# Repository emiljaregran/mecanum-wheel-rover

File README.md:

# mecanum-wheel-rover
A mecanum wheel rover built during a 2 week project.

The wheels are a remix of https://www.thingiverse.com/thing:2473

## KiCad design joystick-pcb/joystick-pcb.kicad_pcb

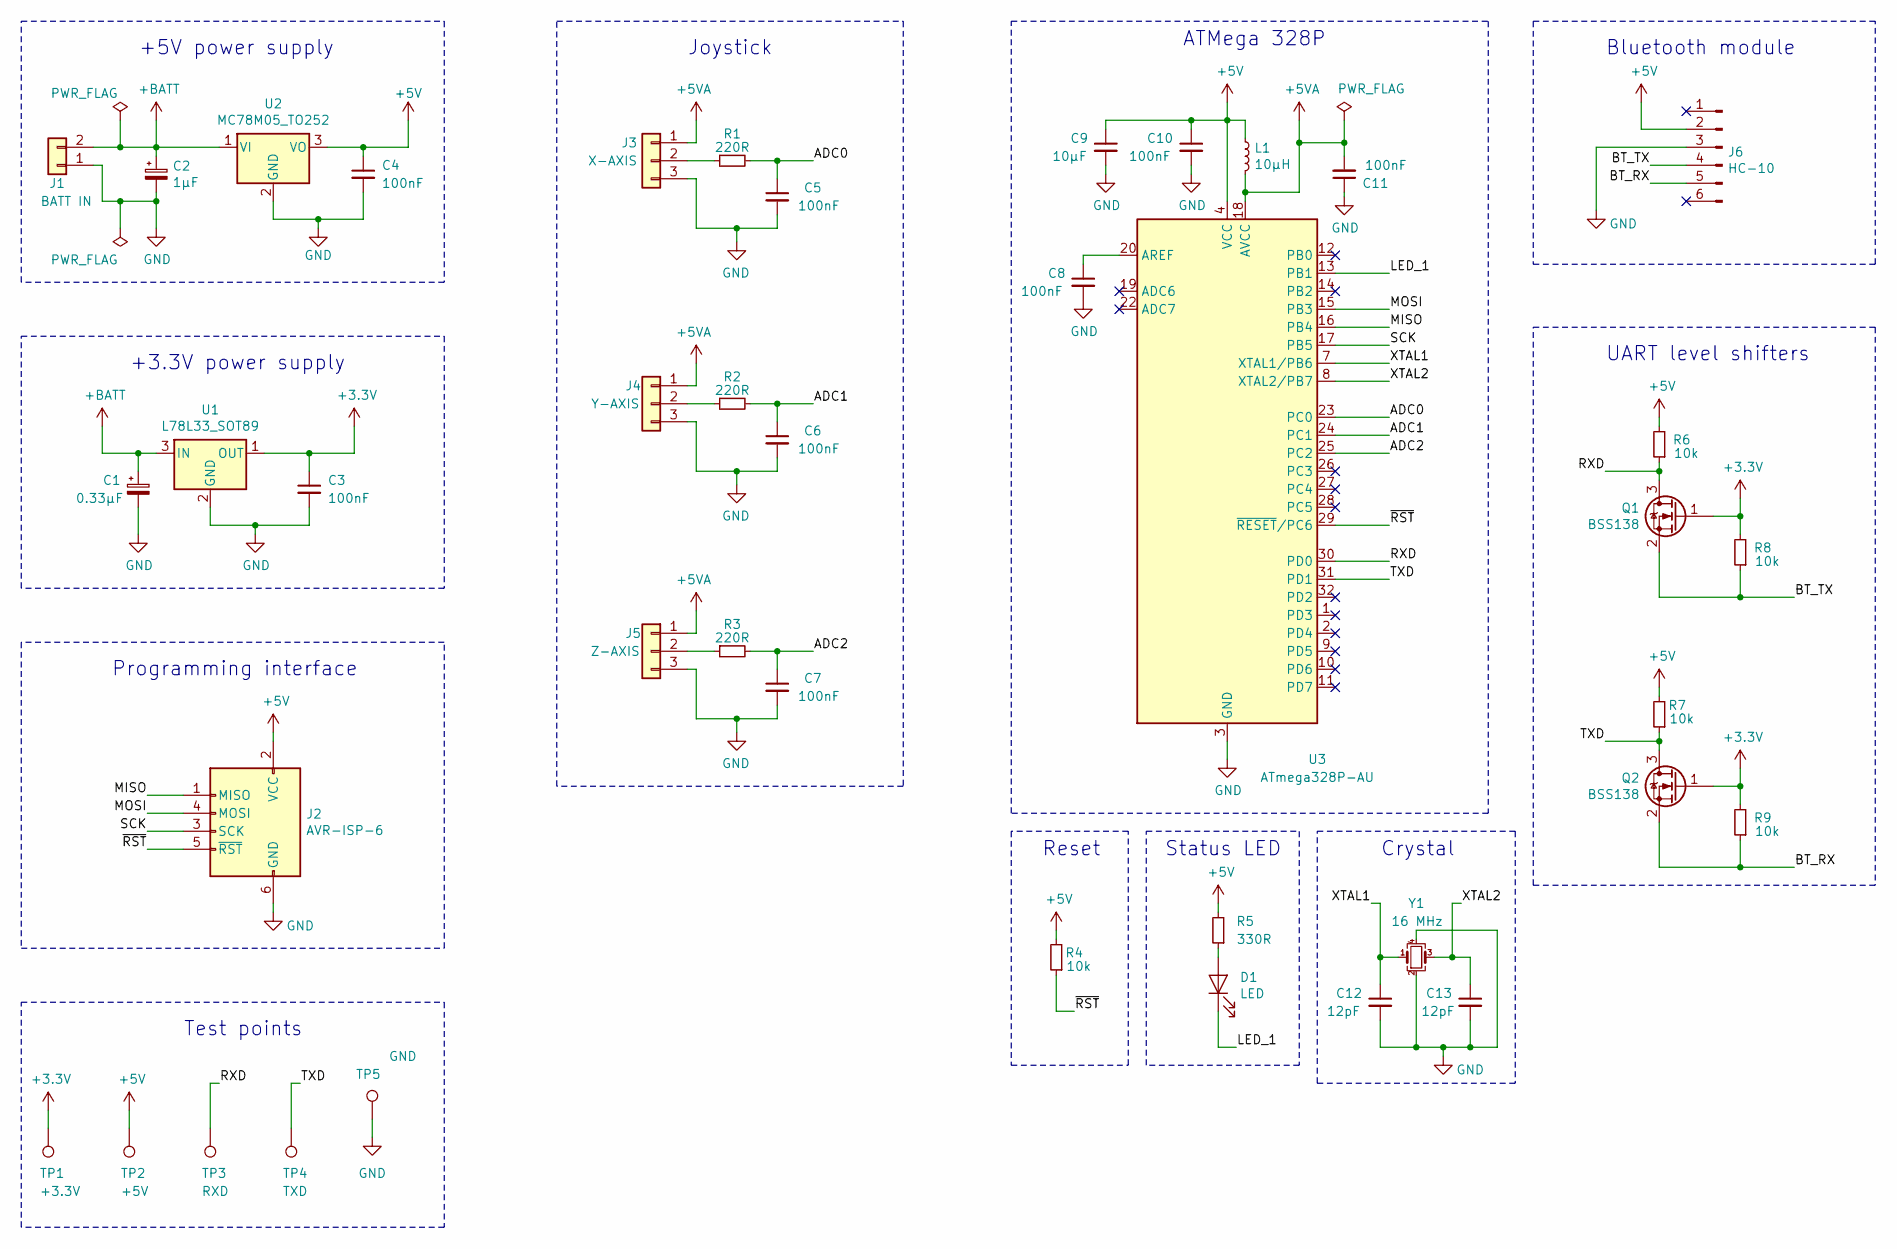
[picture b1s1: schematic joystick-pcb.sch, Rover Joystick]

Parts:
C1: 0.33μF; C_1206_3216Metric_Pad1.42x1.75mm_HandSolder
C2: 1μF; C_1206_3216Metric_Pad1.42x1.75mm_HandSolder
C3, C4, C5, C6, C7, C8, C10, C11: 100nF; C_0603_1608Metric_Pad1.05x0.95mm_HandSolder
C9: 10μF; C_1210_3225Metric_Pad1.42x2.65mm_HandSolder
C12, C13: 12pF; C_0603_1608Metric_Pad1.05x0.95mm_HandSolder
D1: LED; LED_0805_2012Metric_Pad1.15x1.40mm_HandSolder
J1: BATT IN; TerminalBlock_Phoenix_MKDS-1,5-2-5.08_1x02_P5.08mm_Horizont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
J2: AVR-ISP-6; IDC-Header_2x03_P2.54mm_Vertical
J3: X-AXIS; PinHeader_1x03_P2.54mm_Vertical
J4: Y-AXIS; PinHeader_1x03_P2.54mm_Vertical
J5: Z-AXIS; PinHeader_1x03_P2.54mm_Vertical
J6: HC-10; PinHeader_1x06_P2.54mm_Vertical
L1: 10μH; L_0805_2012Metric_Pad1.15x1.40mm_HandSolder
Q1, Q2: BSS138; SOT-23
R1, R2, R3: 220R; R_0603_1608Metric_Pad1.05x0.95mm_HandSolder
R4, R6, R7, R8, R9: 10k; R_0603_1608Metric_Pad1.05x0.95mm_HandSolder
R5: 330R; R_0603_1608Metric_Pad1.05x0.95mm_HandSolder
TP1: +3.3V; TestPoint_THTPad_D2.0mm_Drill1.0mm
TP2: +5V; TestPoint_THTPad_D2.0mm_Drill1.0mm
TP3: RXD; TestPoint_THTPad_D2.0mm_Drill1.0mm
TP4: TXD; TestPoint_THTPad_D2.0mm_Drill1.0mm
TP5: GND; TestPoint_THTPad_D2.0mm_Drill1.0mm
U1: L78L33_SOT89; SOT-89-3
U2: MC78M05_TO252; TO-252-2
U3: ATmega328P-AU; TQFP-32_7x7mm_P0.8mm
Y1: 16 MHz; Crystal_SMD_EuroQuartz_MJ-4Pin_5.0x3.2mm_HandSoldering

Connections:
+3V3: C3.1, Q1.1 (G), Q2.1 (G), R8.2, R9.2, TP1.1, U1.1 (OUT)
+5V: C4.1, C9.1, C10.1, J2.2 (VCC), J6.2, L1.1, R4.2, R5.2, R6.2, R7.2, TP2.1, U2.3 (VO), U3.4 (VCC), U3.6 (VCC)
+5VA: C11.2, J3.1, J4.1, J5.1, L1.2, U3.18 (AVCC)
+BATT: C1.1, C2.1, J1.2, U1.3 (IN), U2.1 (VI)
/ADC0: C5.1, R1.2, U3.23 (PC0)
/ADC1: C6.1, R2.2, U3.24 (PC1)
/ADC2: C7.1, R3.2, U3.25 (PC2)
/BT_RX: J6.5, Q2.2 (S), R9.1
/BT_TX: J6.4, Q1.2 (S), R8.1
/LED_1: D1.1 (K), U3.13 (PB1)
/MISO: J2.1 (MISO), U3.16 (PB4)
/MOSI: J2.4 (MOSI), U3.15 (PB3)
/RXD: Q1.3 (D), R6.1, TP3.1, U3.30 (PD0)
/SCK: J2.3 (SCK), U3.17 (PB5)
/TXD: Q2.3 (D), R7.1, TP4.1, U3.31 (PD1)
/XTAL1: C12.1, U3.7 (XTAL1/PB6), Y1.1
/XTAL2: C13.1, U3.8 (XTAL2/PB7), Y1.3
/~RST: J2.5 (~RST), R4.1, U3.29 (~RESET~/PC6)
GND: C1.2, C2.2, C3.2, C4.2, C5.2, C6.2, C7.2, C8.2, C9.2, C10.2, C11.1, C12.2, C13.2, J1.1, J2.6 (GND), J3.3, J4.3, J5.3, J6.3, TP5.1, U1.2 (GND), U2.2 (GND), U3.3 (GND), U3.5 (GND), U3.21 (GND), Y1.2, Y1.4
unnamed: C8.1, U3.20 (AREF)
unnamed: D1.2 (A), R5.1
unnamed: J3.2, R1.1
unnamed: J4.2, R2.1
unnamed: J5.2, R3.1

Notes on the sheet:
UART level shifters
Bluetooth module
+5V power supply
+3.3V power supply
Programming interface
Test points
Crystal
ATMega 328P
Status LED
Reset
Joystick

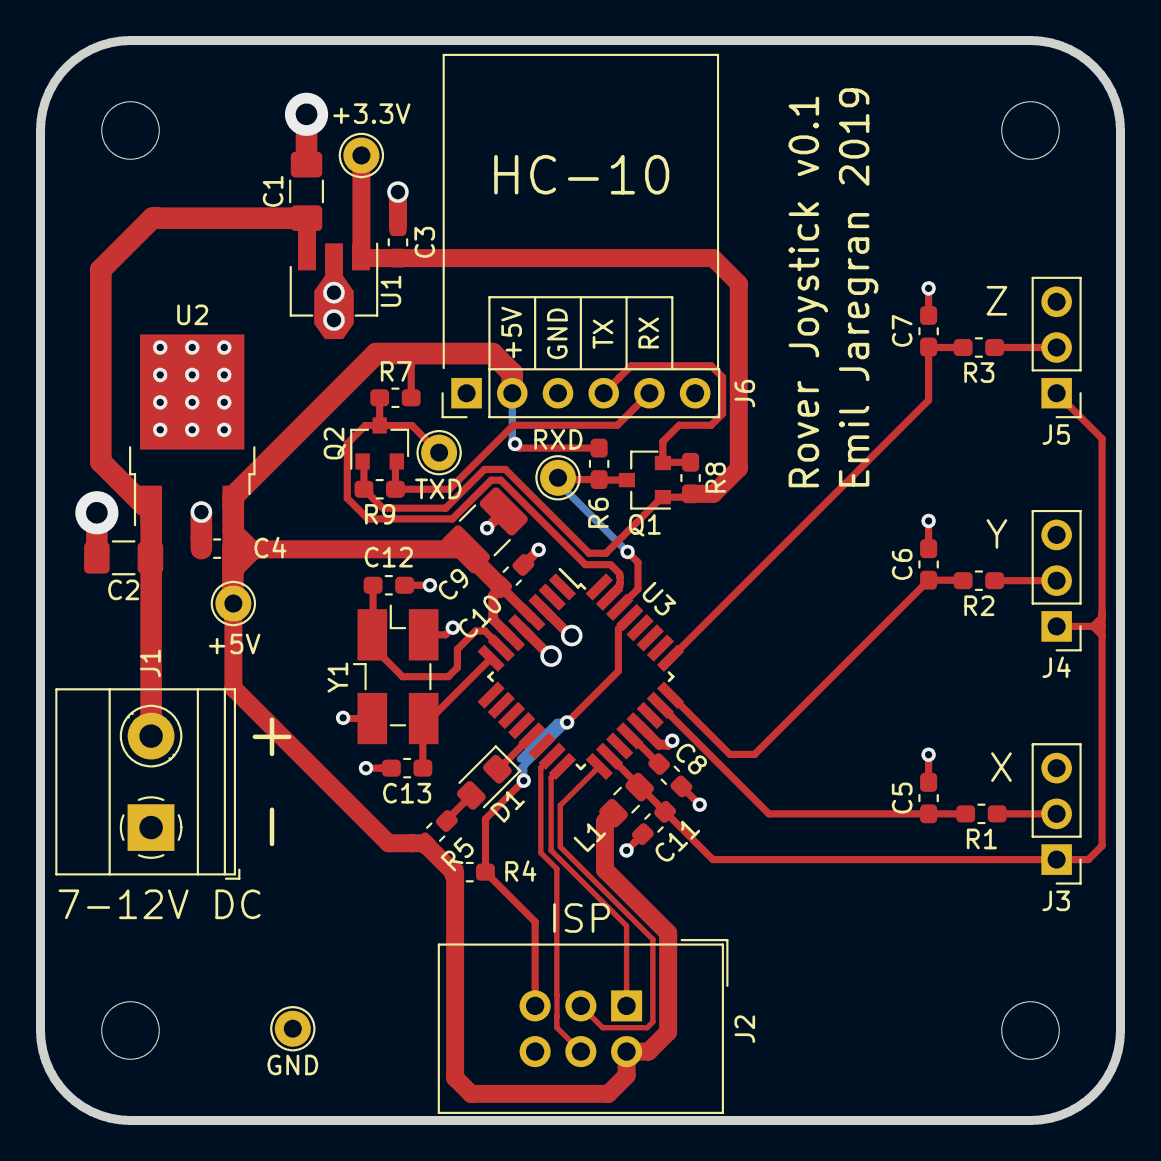
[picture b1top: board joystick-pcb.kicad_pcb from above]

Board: 2 copper layers, 60.0 x 60.0 mm, 41 parts (0 on the bottom side), 24 nets.

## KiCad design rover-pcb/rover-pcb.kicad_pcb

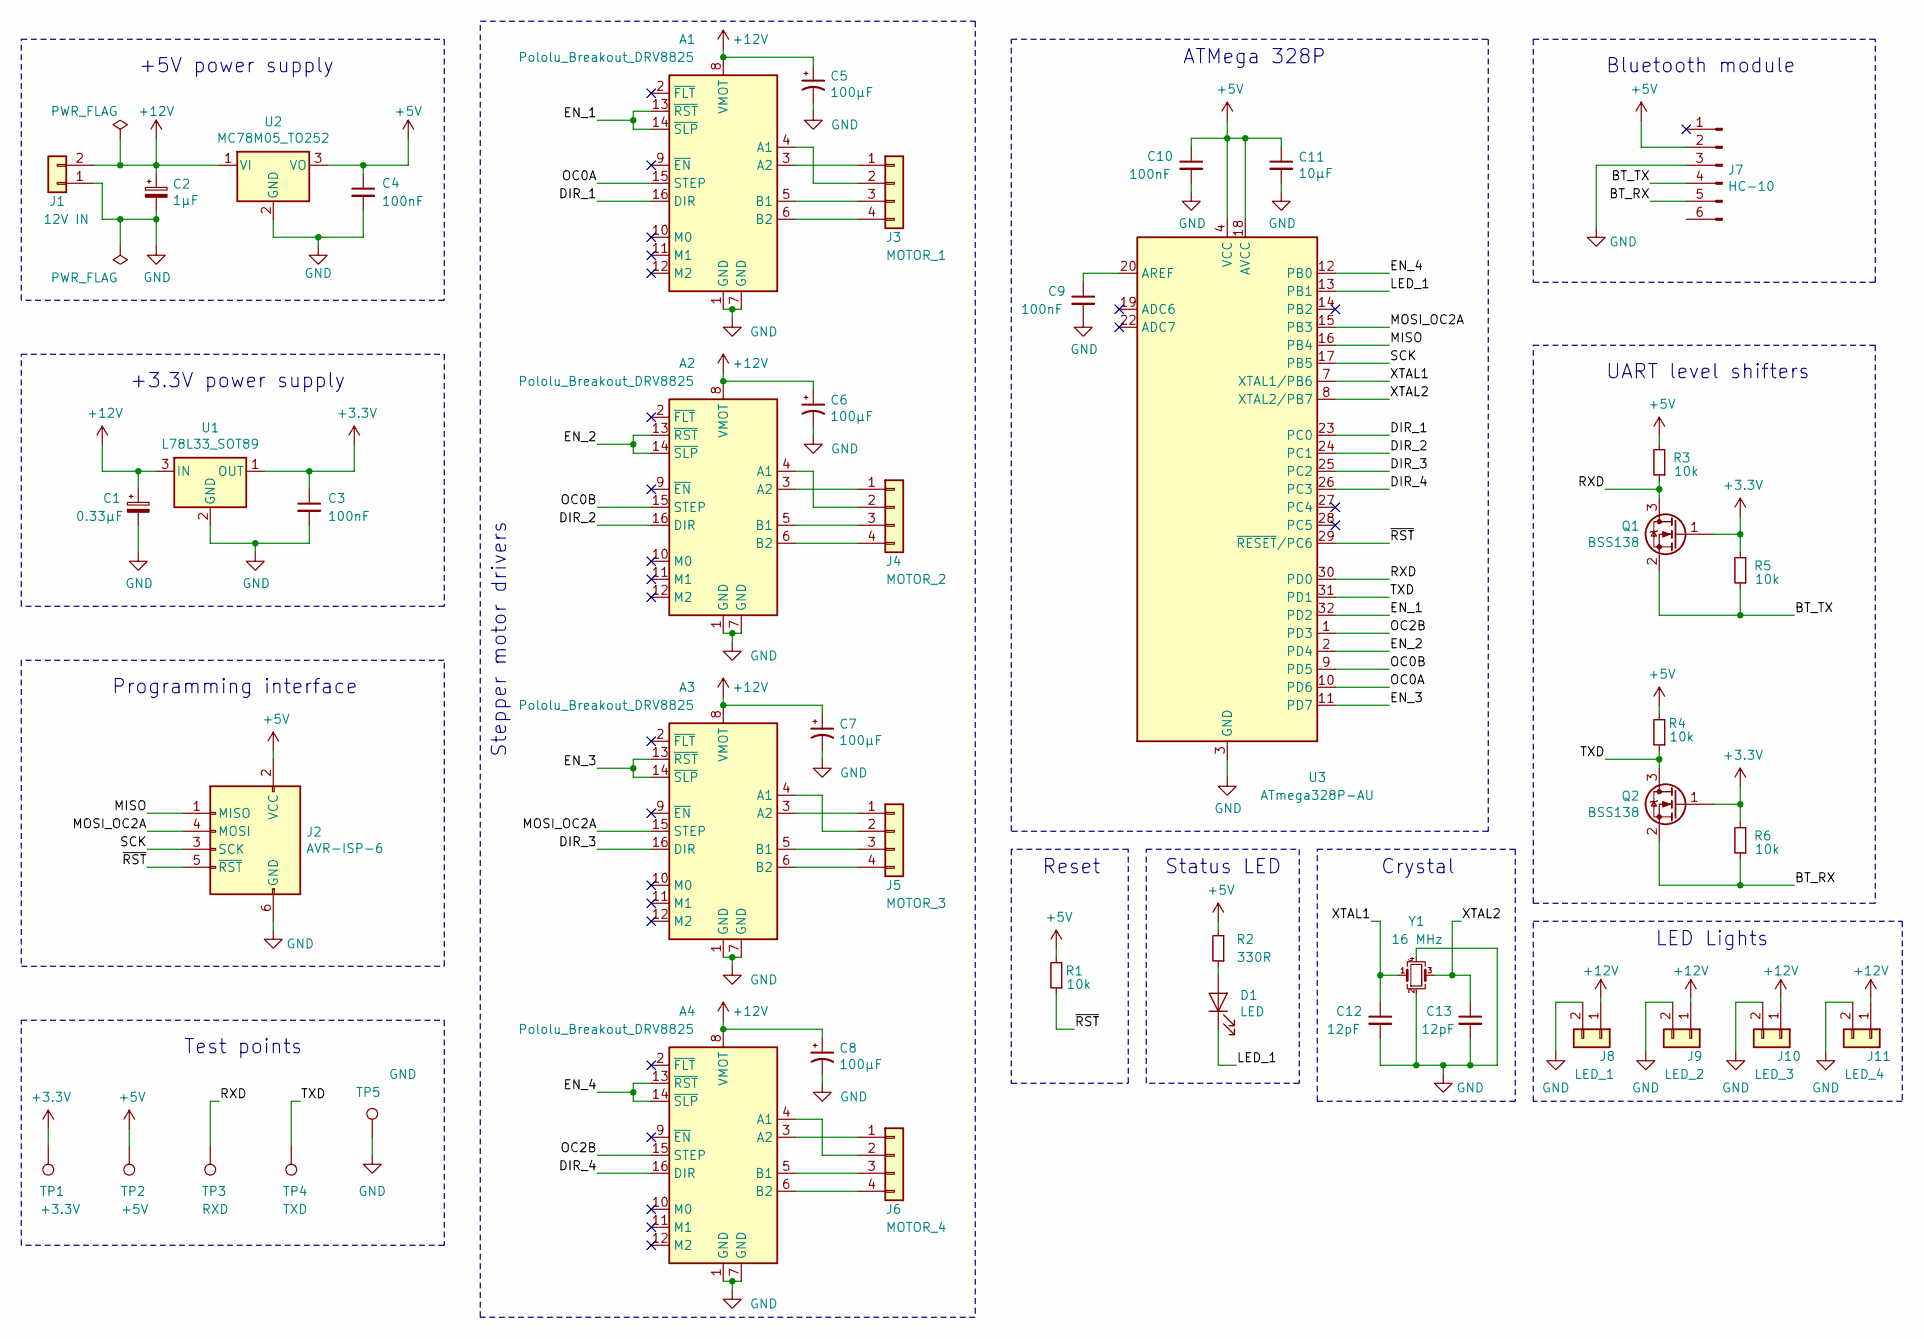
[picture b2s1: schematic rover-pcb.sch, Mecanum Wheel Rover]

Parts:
A1, A2, A3, A4: Pololu_Breakout_DRV8825; Pololu_Breakout-16_15.2x20.3mm
C1: 0.33μF; C_1206_3216Metric_Pad1.42x1.75mm_HandSolder
C2: 1μF; C_1206_3216Metric_Pad1.42x1.75mm_HandSolder
C3, C4, C9, C10: 100nF; C_0603_1608Metric_Pad1.05x0.95mm_HandSolder
C5, C6, C7, C8: 100μF; CP_Elec_6.3x7.7
C11: 10μF; C_1210_3225Metric_Pad1.42x2.65mm_HandSolder
C12, C13: 12pF; C_0603_1608Metric_Pad1.05x0.95mm_HandSolder
D1: LED; LED_0805_2012Metric_Pad1.15x1.40mm_HandSolder
J1: 12V IN; TerminalBlock_Phoenix_MKDS-1,5-2-5.08_1x02_P5.08mm_Horizont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
J2: AVR-ISP-6; IDC-Header_2x03_P2.54mm_Vertical
J3: MOTOR_1; PinHeader_1x04_P2.54mm_Vertical
J4: MOTOR_2; PinHeader_1x04_P2.54mm_Vertical
J5: MOTOR_3; PinHeader_1x04_P2.54mm_Vertical
J6: MOTOR_4; PinHeader_1x04_P2.54mm_Vertical
J7: HC-10; PinHeader_1x06_P2.54mm_Vertical
J8: LED_1; SolderWirePad_1x02_SMD_2x4mm
J9: LED_2; SolderWirePad_1x02_SMD_2x4mm
J10: LED_3; SolderWirePad_1x02_SMD_2x4mm
J11: LED_4; SolderWirePad_1x02_SMD_2x4mm
Q1, Q2: BSS138; SOT-23
R1, R3, R4, R5, R6: 10k; R_0603_1608Metric_Pad1.05x0.95mm_HandSolder
R2: 330R; R_0603_1608Metric_Pad1.05x0.95mm_HandSolder
TP1: +3.3V; TestPoint_THTPad_D2.0mm_Drill1.0mm
TP2: +5V; TestPoint_THTPad_D2.0mm_Drill1.0mm
TP3: RXD; TestPoint_THTPad_D2.0mm_Drill1.0mm
TP4: TXD; TestPoint_THTPad_D2.0mm_Drill1.0mm
TP5: GND; TestPoint_THTPad_D2.0mm_Drill1.0mm
U1: L78L33_SOT89; SOT-89-3
U2: MC78M05_TO252; TO-252-2
U3: ATmega328P-AU; TQFP-32_7x7mm_P0.8mm
Y1: 16 MHz; Crystal_SMD_EuroQuartz_MJ-4Pin_5.0x3.2mm_HandSoldering

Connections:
+3V3: C3.1, Q1.1 (G), Q2.1 (G), R5.2, R6.2, TP1.1, U1.1 (OUT)
+5V: C4.1, C10.1, C11.1, J2.2 (VCC), J7.2, R1.2, R2.2, R3.2, R4.2, TP2.1, U2.3 (VO), U3.4 (VCC), U3.6 (VCC), U3.18 (AVCC)
+12V: A1.8 (VMOT), A2.8 (VMOT), A3.8 (VMOT), A4.8 (VMOT), C1.1, C2.1, C5.1, C6.1, C7.1, C8.1, J1.2, J8.1, J9.1, J10.1, J11.1, U1.3 (IN), U2.1 (VI)
/BT_RX: J7.5, Q2.2 (S), R6.1
/BT_TX: J7.4, Q1.2 (S), R5.1
/DIR_1: A1.16 (DIR), U3.23 (PC0)
/DIR_2: A2.16 (DIR), U3.24 (PC1)
/DIR_3: A3.16 (DIR), U3.25 (PC2)
/DIR_4: A4.16 (DIR), U3.26 (PC3)
/EN_1: A1.13 (~RST), A1.14 (~SLP), U3.32 (PD2)
/EN_2: A2.13 (~RST), A2.14 (~SLP), U3.2 (PD4)
/EN_3: A3.13 (~RST), A3.14 (~SLP), U3.11 (PD7)
/EN_4: A4.13 (~RST), A4.14 (~SLP), U3.12 (PB0)
/LED_1: D1.1 (K), U3.13 (PB1)
/MISO: J2.1 (MISO), U3.16 (PB4)
/MOSI_OC2A: A3.15 (STEP), J2.4 (MOSI), U3.15 (PB3)
/OC0A: A1.15 (STEP), U3.10 (PD6)
/OC0B: A2.15 (STEP), U3.9 (PD5)
/OC2B: A4.15 (STEP), U3.1 (PD3)
/RXD: Q1.3 (D), R3.1, TP3.1, U3.30 (PD0)
/SCK: J2.3 (SCK), U3.17 (PB5)
/TXD: Q2.3 (D), R4.1, TP4.1, U3.31 (PD1)
/XTAL1: C12.1, U3.7 (XTAL1/PB6), Y1.1
/XTAL2: C13.1, U3.8 (XTAL2/PB7), Y1.3
/~RST: J2.5 (~RST), R1.1, U3.29 (~RESET~/PC6)
GND: A1.1 (GND), A1.7 (GND), A2.1 (GND), A2.7 (GND), A3.1 (GND), A3.7 (GND), A4.1 (GND), A4.7 (GND), C1.2, C2.2, C3.2, C4.2, C5.2, C6.2, C7.2, C8.2, C9.2, C10.2, C11.2, C12.2, C13.2, J1.1, J2.6 (GND), J7.3, J8.2, J9.2, J10.2, J11.2, TP5.1, U1.2 (GND), U2.2 (GND), U3.3 (GND), U3.5 (GND), U3.21 (GND), Y1.2, Y1.4
unnamed: A1.3 (A2), J3.1
unnamed: A1.4 (A1), J3.2
unnamed: A1.5 (B1), J3.3
unnamed: A1.6 (B2), J3.4
unnamed: A2.3 (A2), J4.1
unnamed: A2.4 (A1), J4.2
unnamed: A2.5 (B1), J4.3
unnamed: A2.6 (B2), J4.4
unnamed: A3.3 (A2), J5.1
unnamed: A3.4 (A1), J5.2
unnamed: A3.5 (B1), J5.3
unnamed: A3.6 (B2), J5.4
unnamed: A4.3 (A2), J6.1
unnamed: A4.4 (A1), J6.2
unnamed: A4.5 (B1), J6.3
unnamed: A4.6 (B2), J6.4
unnamed: C9.1, U3.20 (AREF)
unnamed: D1.2 (A), R2.1

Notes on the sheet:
UART level shifters
Bluetooth module
+5V power supply
+3.3V power supply
Programming interface
Test points
Crystal
ATMega 328P
Status LED
Stepper motor drivers
Reset
LED Lights

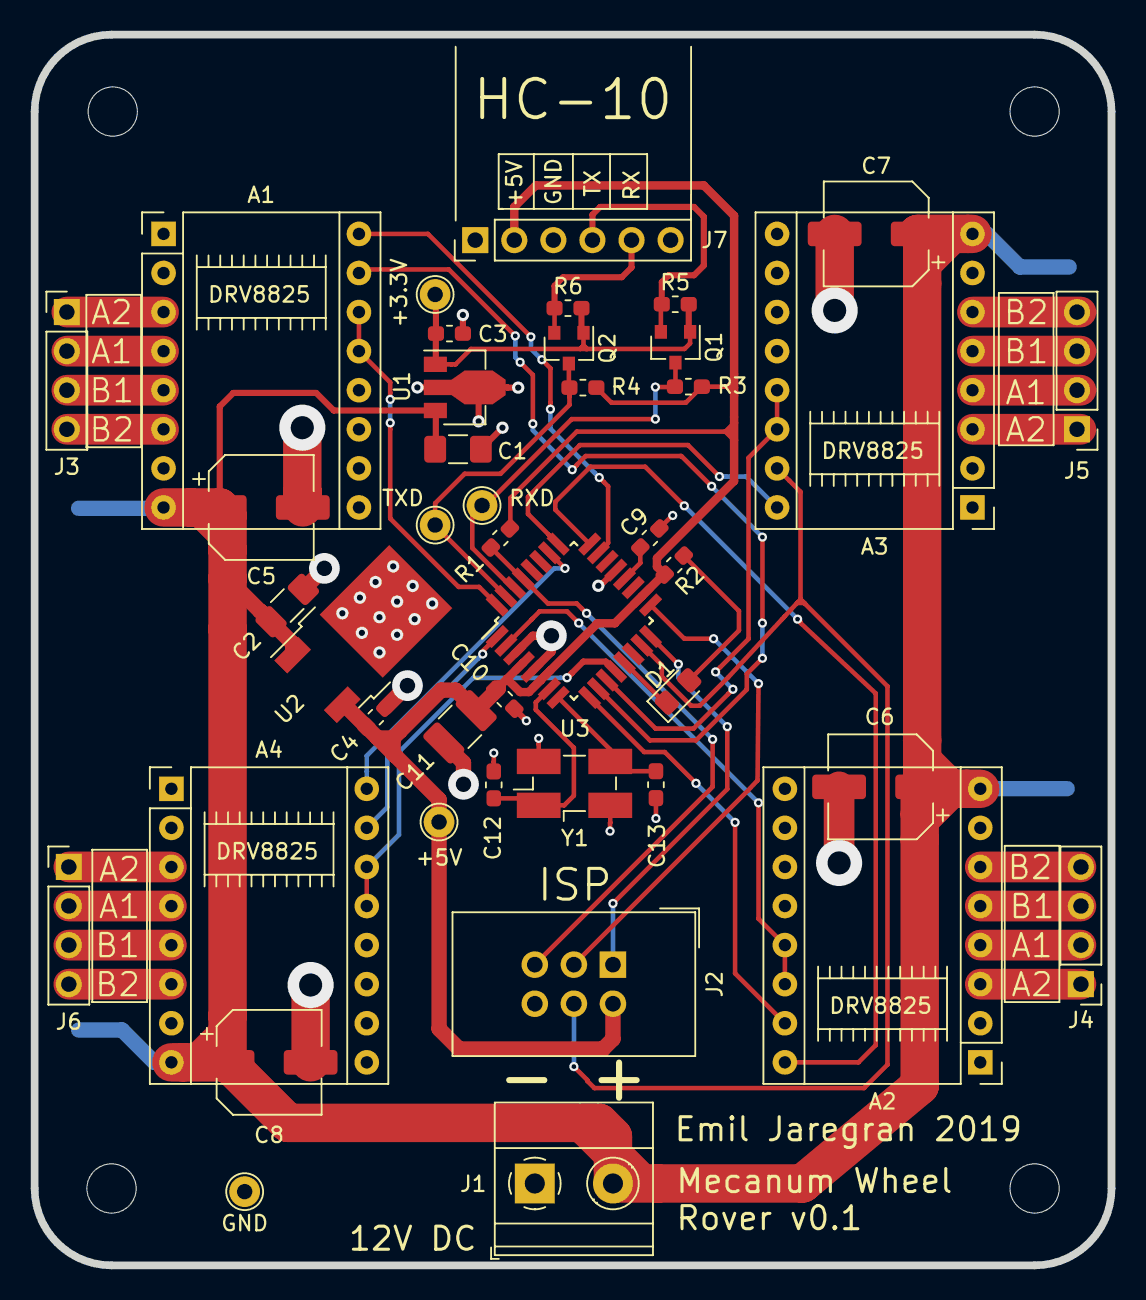
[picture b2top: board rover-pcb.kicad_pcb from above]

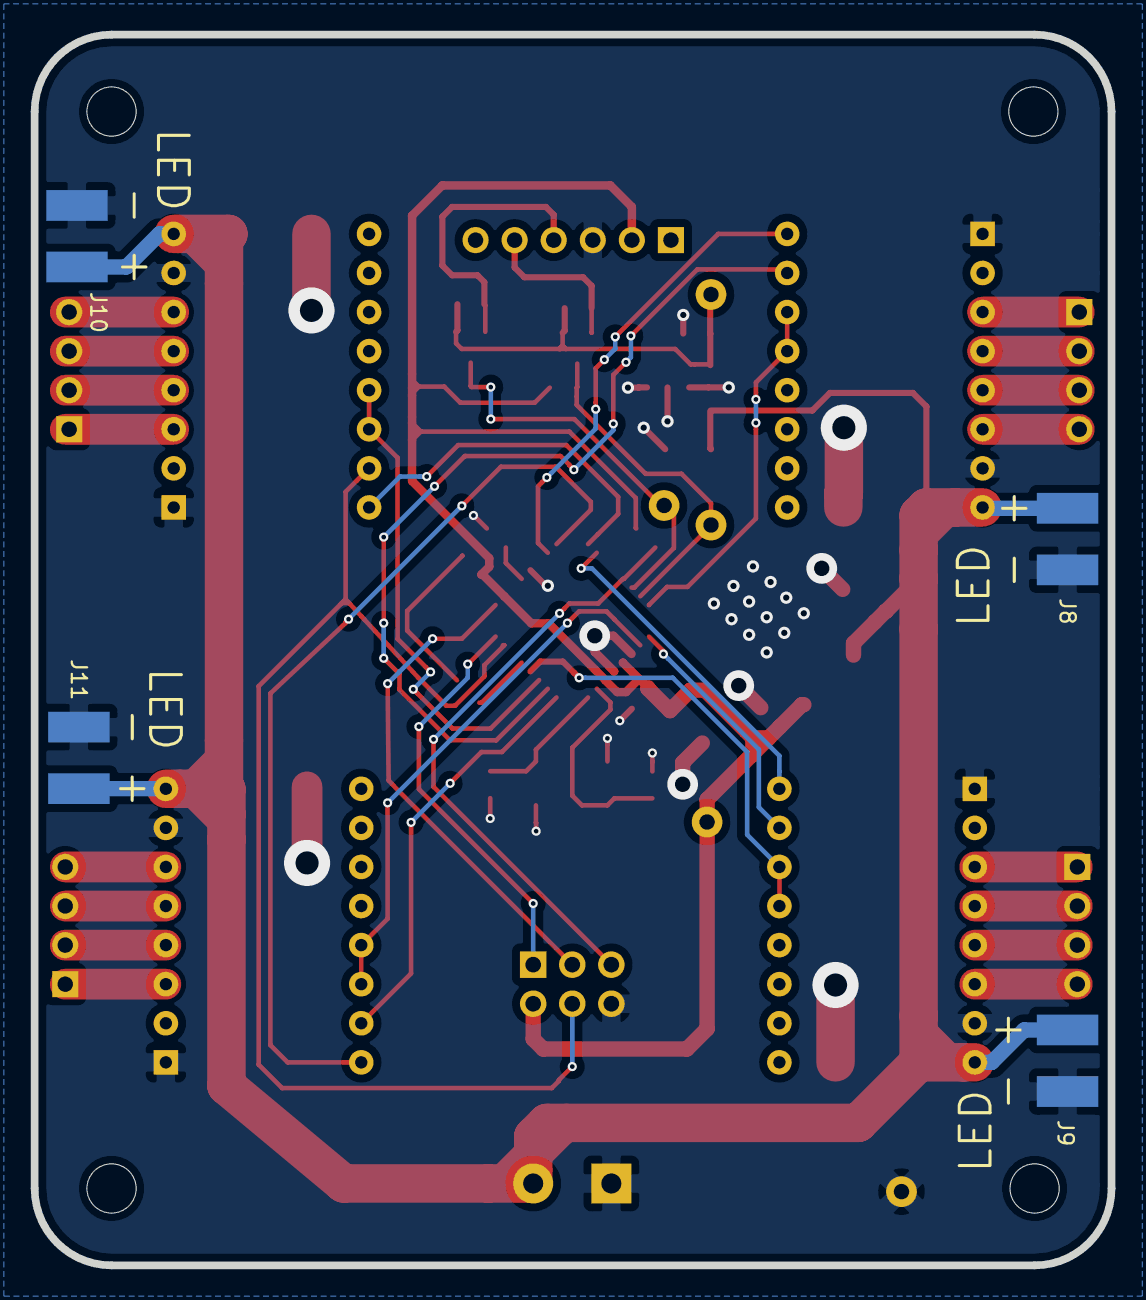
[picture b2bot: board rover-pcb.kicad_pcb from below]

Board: 2 copper layers, 70.0 x 80.0 mm, 46 parts (4 on the bottom side), 44 nets.

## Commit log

2019-09-30 Adding schematic for Rover PCB.
2019-09-30 Adding Rover PCB layout.
2019-10-01 Adding pads for external LEDs.
2019-10-01 Adding Joystick PCB.
2019-10-08 Adding CAD files.
2019-10-08 Adding first revision of joystick firmware.
2019-10-08 Scaling axis values between -128 and 127.
2019-10-08 Experimental version with struct as data package.
2019-10-08 First revision of rover firmware.
2019-10-08 Set LED to OFF at start up.
2019-10-09 Refactored joystick firmware.
2019-10-09 One wheel drive test-rover.
2019-10-09 Sideway motion implemented.
2019-10-10 Nine directions for rover movement implemented.
2019-10-11 Eleven directions movement, plus some refactoring.
2019-10-11 Refactor rover movements.
2019-10-11 Implemented acceleration and de-acceleration.
2019-10-11 Adding drive north turn cw.
2019-10-11 Re-factoring and clean up.
2019-10-11 All motions implemented.
2019-10-12 Adding fan mount and refactor rover movement.
2019-10-12 Implementing kill switch.
2019-10-12 Implementing status LED and bugfix for ENABLE-pin.
2019-10-12 Changed joystick deadband.
2019-10-12 Adding CAD model for fan mount.
2019-10-14 Fixed rover turned wrong directing driving north.
